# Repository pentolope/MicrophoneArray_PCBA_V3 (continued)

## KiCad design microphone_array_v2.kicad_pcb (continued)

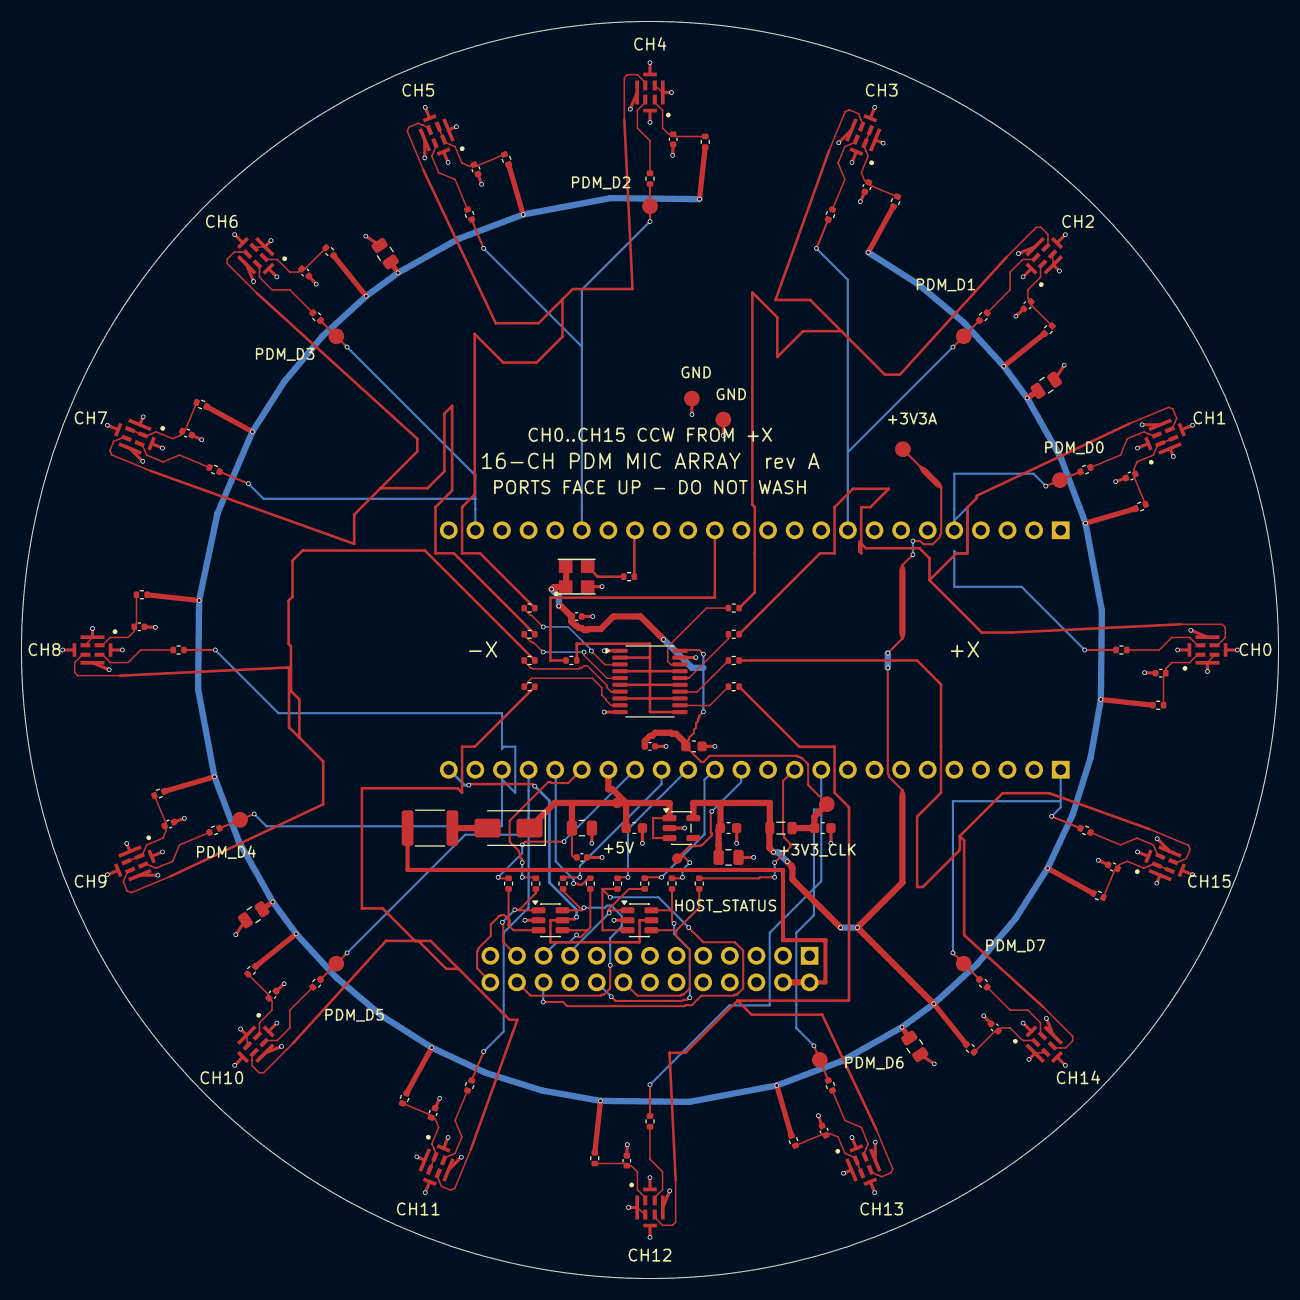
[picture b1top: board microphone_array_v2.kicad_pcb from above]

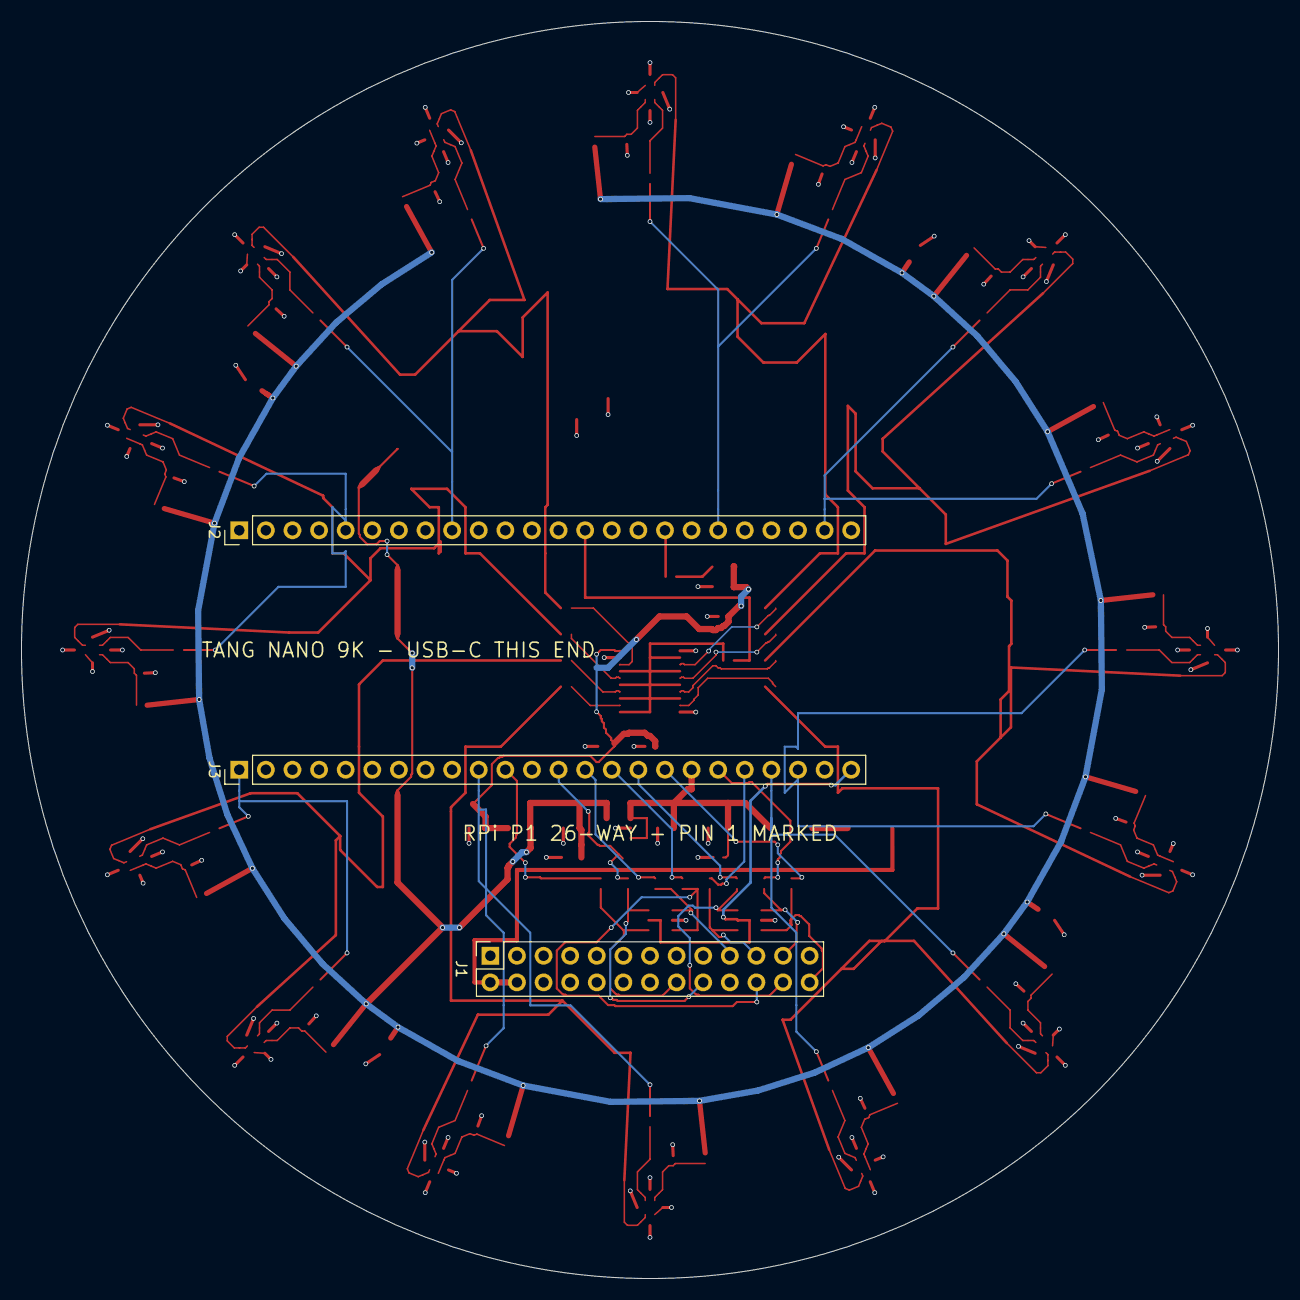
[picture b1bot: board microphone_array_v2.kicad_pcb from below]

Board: 4 copper layers, 120.0 x 120.0 mm, 120 parts (3 on the bottom side), 83 nets.

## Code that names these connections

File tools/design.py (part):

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PI_HEADER = {
    2: "PI_5V", 4: "PI_5V",
    6: "GND", 9: "GND", 14: "GND", 20: "GND", 25: "GND",
    16: "PI_SYNC",     # GPIO23
    18: "PI_STATUS",   # GPIO24
    19: "PI_MOSI",     # GPIO10
    21: "PI_MISO",     # GPIO9
    22: "PI_IRQ",      # GPIO25
    23: "PI_SCLK",     # GPIO11
    24: "PI_CS_N",     # GPIO8  / CE0
    26: "PI_RESET_N",  # GPIO7  / CE1
}

# Ordered left to right by where each signal leaves the Pi header, so the
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# from the connector at the bottom, past the header and both socket rows, to
# the top row - for no reason.
#
# The 25 MHz SPI is kept on non-HDMI pins wherever possible. Only SPI_CS_N
# lands on an HDMI-shared pin, and it is static for the duration of a burst.
TANG_NET_MAP = {
    ("J2", 5): "PDM_D0",          # FPGA 25, pair 0 at azimuth 11 deg
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    ("J3", 1): "PDM_D7",          # FPGA 63, pair 7 at 326 deg
    ("J3", 10): "PDM_D6",         # FPGA 77, pair 6 at 281 deg
    # Host pins are in the same left-to-right order as the resistor row that
    # feeds them. SPI_SCLK and SPI_MISO are placed on the two non-HDMI pins,
    # being the pair whose edges the 25 MHz link actually depends on.
    ("J3", 11): "HOST_SYNC",      # FPGA 76, not HDMI-shared
    ("J3", 13): "HOST_STATUS",    # FPGA 74
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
